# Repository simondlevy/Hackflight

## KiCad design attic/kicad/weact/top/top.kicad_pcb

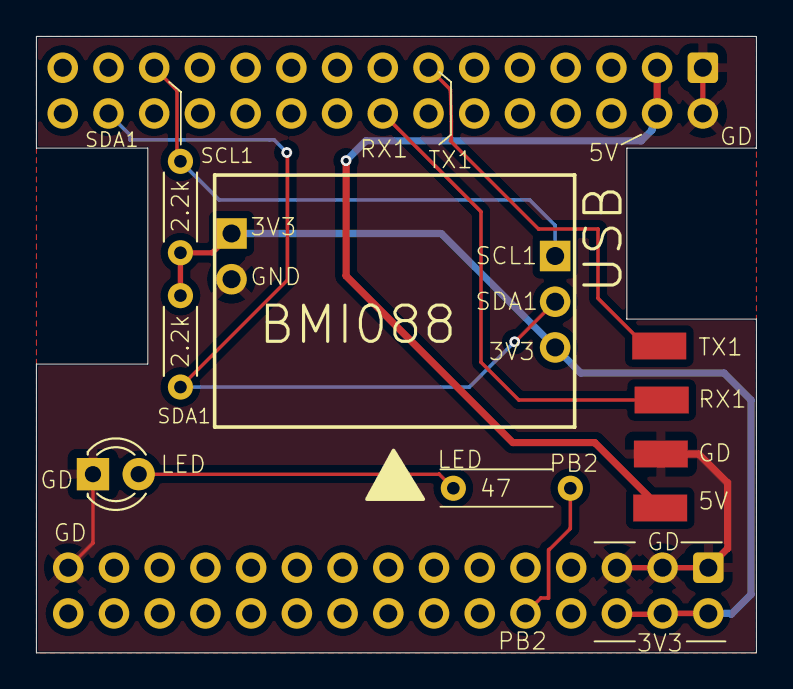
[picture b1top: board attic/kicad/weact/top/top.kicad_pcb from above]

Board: 2 copper layers, 40.0 x 34.2 mm, 12 parts (0 on the bottom side), 9 nets.

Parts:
2.2k, 2.2k#2: 2.2k Ohms; R_Axial_DIN0204_L3.6mm_D1.6mm_P5.08mm_Horizontal
47: 47 Ohms; R_Axial_DIN0204_L3.6mm_D1.6mm_P5.08mm_Horizontal
D1: LED; LED_D3.0mm
GND_PAD18, GND_PAD19, GND_PAD20, GND_PAD21: Conn_01x01; SolderWirePad_1x01_SMD_5x10mm
J1, J1#2: Conn_01x15_MountingPin; IDC-Header_2x15_P2.54mm_Vertical
Motor5: Conn_01x03_Female; PinHeader_1x03_P2.54mm_Vertical
PMW3901_PWR2: Conn_01x02_Female; PinHeader_1x02_P2.54mm_Vertical

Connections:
/3V3: 2.2k.2, 2.2k#2.2, J1.2, J1.4, J1.6, Motor5.3, PMW3901_PWR2.1
/5V: GND_PAD19.1, J1#2.3, J1#2.4
/GND: D1.1 (K), GND_PAD18.1, J1.1, J1.3, J1.5, J1.29, J1#2.1, J1#2.2, PMW3901_PWR2.2
/LED_RAW: 47.2, J1.10
/RX1: GND_PAD20.1, J1#2.16
/SCL1: 2.2k.1, J1#2.25, Motor5.1
/SDA1: 2.2k#2.1, J1#2.28, Motor5.2
/TX1: GND_PAD21.1, J1#2.13
unnamed: 47.1, D1.2 (A)

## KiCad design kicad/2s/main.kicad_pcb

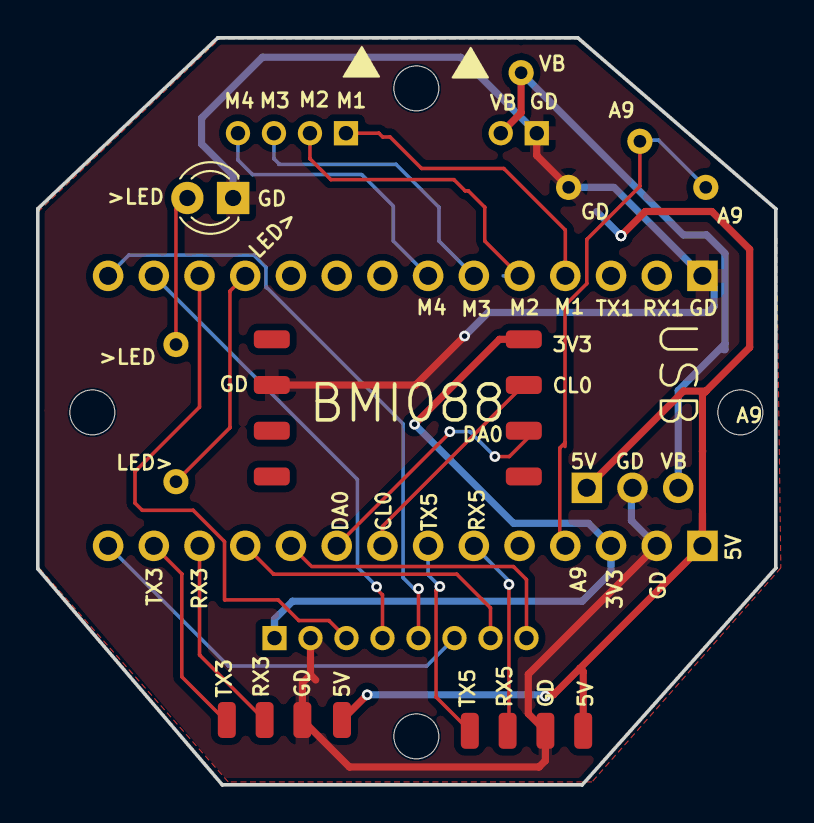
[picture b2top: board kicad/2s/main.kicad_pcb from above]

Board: 2 copper layers, 41.0 x 41.5 mm, 30 parts (0 on the bottom side), 23 nets.

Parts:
D1: LED; LED_D3.0mm_FlatTop
H1, H2, H3, H4: MountingHole; MountingHole_2.5mm
J1: Conn_01x14; PinSocket_1x14_P2.54mm_Vertical
J2: Conn_01x14_Socket; PinSocket_1x14_P2.54mm_Vertical
J3, J5, J7, J8, J9, J10, J11, J12, J13, J14, J17, J18, J19, J20, J21, J22: Conn_01x01_Pin; SolderWirePad_1x01_SMD_1x2mm
J4: Conn_01x03_Socket; PinHeader_1x03_P2.54mm_Vertical
J6: Conn_01x08; PinSocket_1x08_P2.00mm_Vertical
J15: Conn_01x02; PinSocket_1x02_P2.00mm_Vertical
J16: Conn_01x04; PinSocket_1x04_P2.00mm_Vertical
R1: R_LED; R_Axial_DIN0204_L3.6mm_D1.6mm_P7.62mm_Horizontal
R2: R1; R_Axial_DIN0204_L3.6mm_D1.6mm_P7.62mm_Horizontal
R3: R2; R_Axial_DIN0204_L3.6mm_D1.6mm_P7.62mm_Horizontal

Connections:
/3V3: J2.3, J6.1, J10.1 (Pin_1_1)
/5V: J2.1, J4.1, J14.1 (Pin_1_1), J20.1 (Pin_1_1)
/A9: J2.4, R2.1, R3.2
/CS: J1.12, J6.3
/GND: D1.1 (K), J1.1, J2.2, J3.1 (Pin_1_1), J4.2, J5.1 (Pin_1_1), J6.2, J15.1, J19.1 (Pin_1_1), R3.1
/LED: J1.11, R1.2
/M1: J1.4, J16.1
/M2: J1.5, J16.2
/M3: J1.6, J16.3
/M4: J1.7, J16.4
/MISO: J1.14, J6.5
/MOSI: J1.13, J6.4
/RX3: J2.12, J17.1 (Pin_1_1)
/RX5: J2.6, J21.1 (Pin_1_1)
/SCK: J2.14, J6.6
/SCL0: J2.8, J11.1 (Pin_1_1)
/SCL1: J2.11, J6.7
/SDA0: J2.9, J12.1 (Pin_1_1)
/SDA1: J2.10, J6.8
/TX3: J2.13, J18.1 (Pin_1_1)
/TX5: J2.7, J22.1 (Pin_1_1)
/VBAT: J4.3, J15.2, R2.2
unnamed: D1.2 (A), R1.1

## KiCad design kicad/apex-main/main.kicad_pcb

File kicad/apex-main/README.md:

# BOM, in order of soldering

Note: I recommend using Scotch tape to mask the pins you're not currently
soldering, and doing a continunity check for bridges/shorts after each step:

1. [Pololu 5V Step-Up/Step-Down Voltage Regulator S7V7F5](https://www.pololu.com/product/2119), on bottom, using 1-2mm chisel/bevel tip.

2. [28AWG silicone-insulated wire](https://www.amazon.com/BOJACK-Flexible-Silicone-Electric-Stripper/dp/B09Y89X5CV) for hover-deck, 
   protruding from bottom, using 0.2-0.8mm fine/conical tip.

3. [SHUTTLE BOARD 3.0 BMI088](https://www.digikey.com/en/products/detail/bosch-sensortec/SHUTTLE-BOARD-3-0-BMI088/14617528), on top, 
using 0.2-0.8mm fine/conical tip.  To avoid soldering a bridge (short circuit), you should solder only the four indicated
pins (3V3, GND, SDA, SCL), and in the bottom corners for added mounting security.

4. 28AWG silicone-insulates wires to 4-in-1 ESC, protruding from bottom, using 0.2-0.8mm fine/conical tip.
Most 4-in-1 ESCs come with this [connector](../../media/4-in-1-esc-wiring.jpg), or you can build one yourself
using a kit like
[this](https://www.amazon.com/Teansic-Connector-Pre-Crimped-Housing-Controller/dp/B0D5X6BY5Z/ref=sr_1_1_sspa?crid=1UNL8YQMAGJI0).

5. 220Ω resitor, on bottom, using 1-2mm chisel/bevel tip.

6. [LED](https://lighthouseleds.com/1-8mm-2mm-led-red-ultra-bright.html), on top, using 1-2mm chisel/bevel tip.

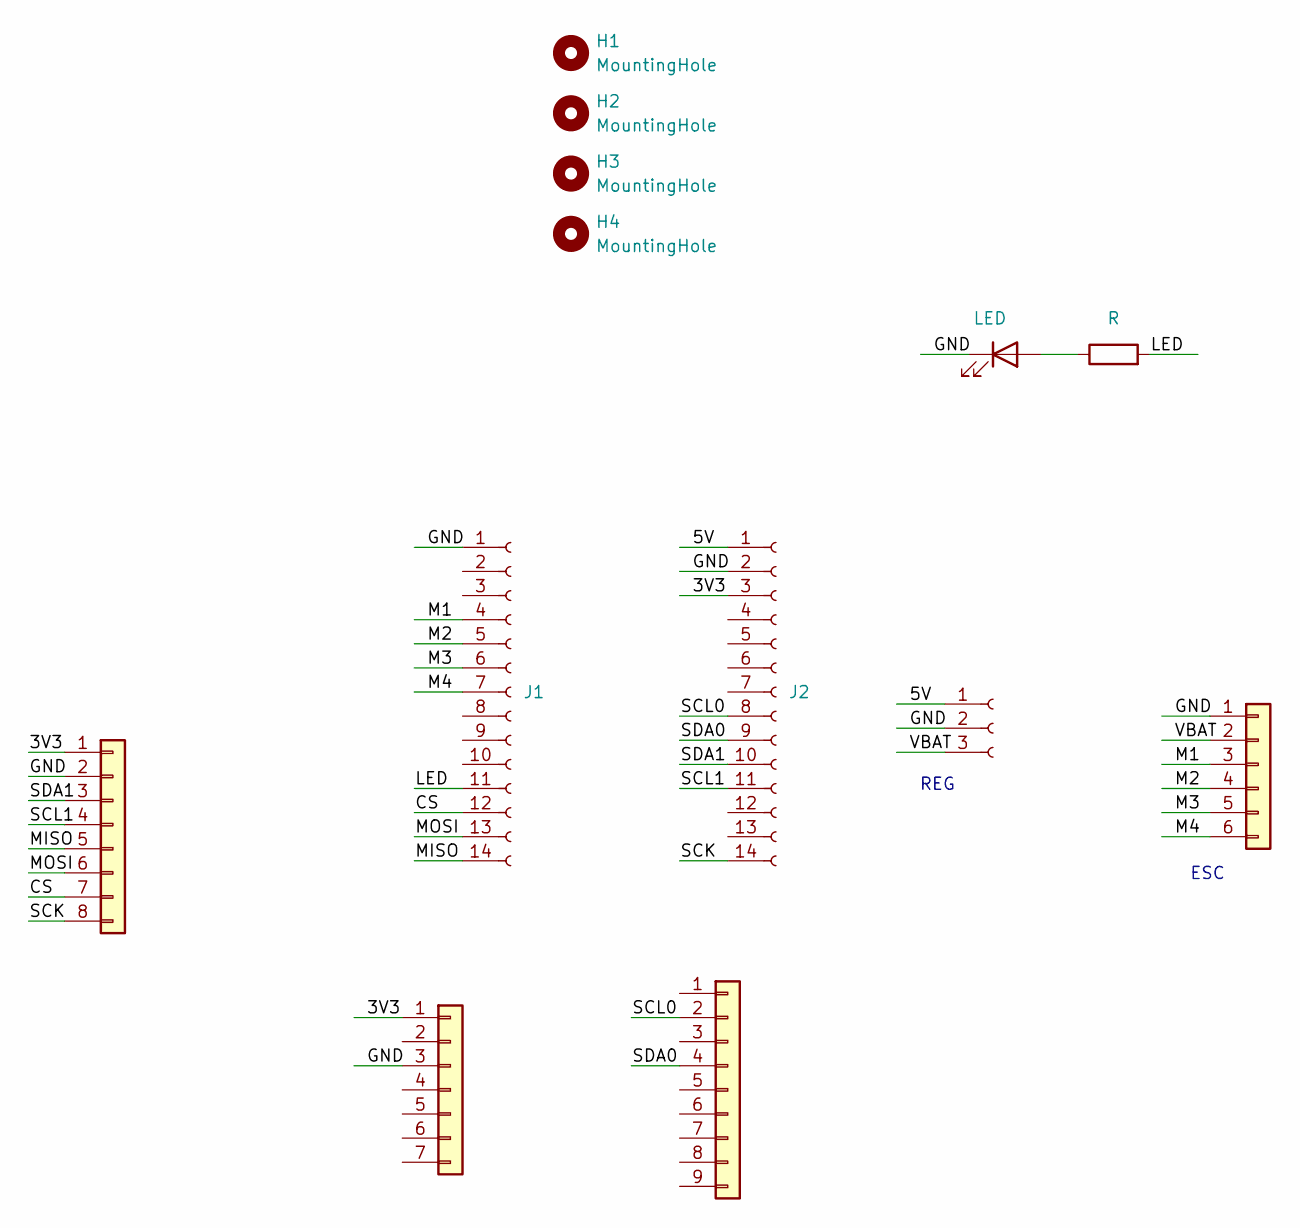
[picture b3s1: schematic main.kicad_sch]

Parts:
D1: LED; LED_D3.0mm_FlatTop
H1, H2, H3, H4: MountingHole; MountingHole_2.1mm
J1: Conn_01x14; PinSocket_1x14_P2.54mm_Vertical
J2: Conn_01x14_Socket; PinSocket_1x14_P2.54mm_Vertical
J4: Conn_01x03_Socket; PinHeader_1x03_P2.54mm_Vertical
J5: Conn_01x06; PinSocket_1x06_P2.00mm_Vertical
J6: Conn_01x08; PinSocket_1x08_P2.00mm_Vertical
J7: Conn_01x07; PinHeader_1x07_P1.27mm_Vertical
J8: Conn_01x09; PinHeader_1x09_P1.27mm_Vertical
R1: R; R_Axial_DIN0204_L3.6mm_D1.6mm_P7.62mm_Horizontal

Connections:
/3V3: J2.3, J6.1, J7.1
/5V: J2.1, J4.1
/CS: J1.12, J6.7
/GND: D1.1 (K), J1.1, J2.2, J4.2, J5.1, J6.2, J7.3
/LED: J1.11, R1.2
/M1: J1.4, J5.3
/M2: J1.5, J5.4
/M3: J1.6, J5.5
/M4: J1.7, J5.6
/MISO: J1.14, J6.5
/MOSI: J1.13, J6.6
/SCK: J2.14, J6.8
/SCL0: J2.8, J8.2
/SCL1: J2.11, J6.4
/SDA0: J2.9, J8.4
/SDA1: J2.10, J6.3
/VBAT: J4.3, J5.2
unnamed: D1.2 (A), R1.1

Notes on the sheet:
ESC
REG

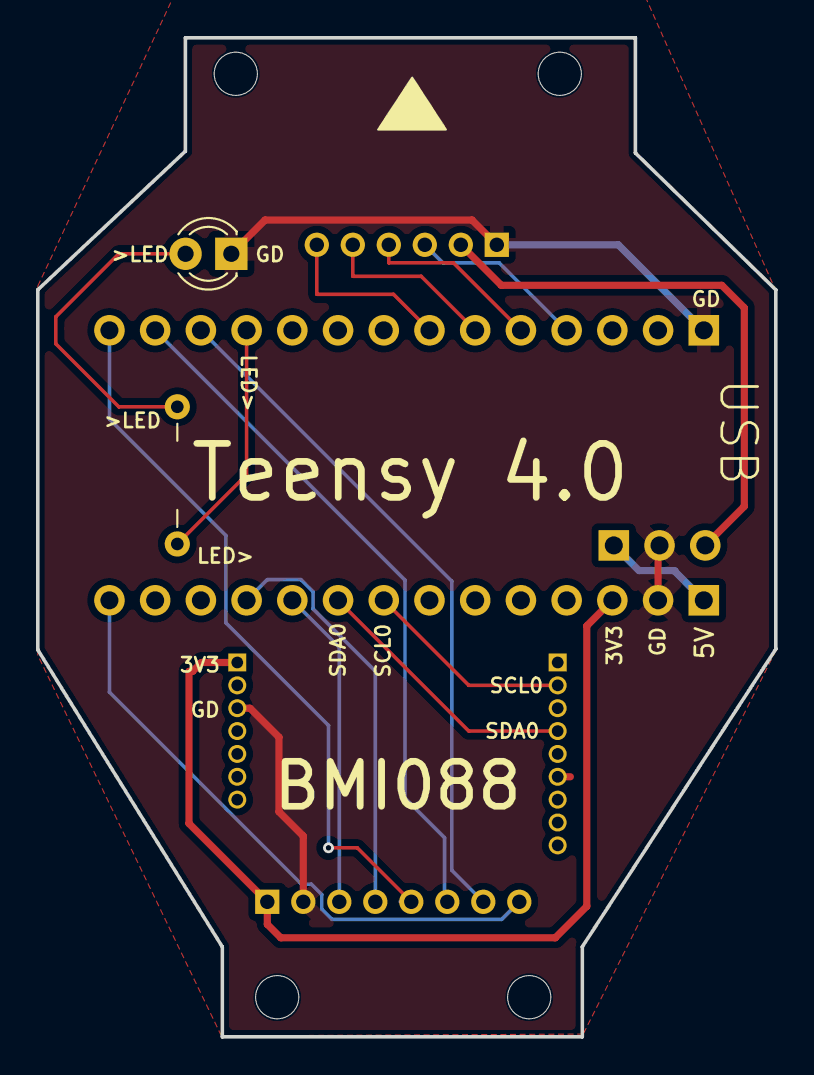
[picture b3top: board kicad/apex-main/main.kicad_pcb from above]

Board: 2 copper layers, 41.0 x 55.5 mm, 16 parts (0 on the bottom side), 18 nets.

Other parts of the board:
H1#2, H1#3, H1#4: MountingHole; MountingHole_2.1mm

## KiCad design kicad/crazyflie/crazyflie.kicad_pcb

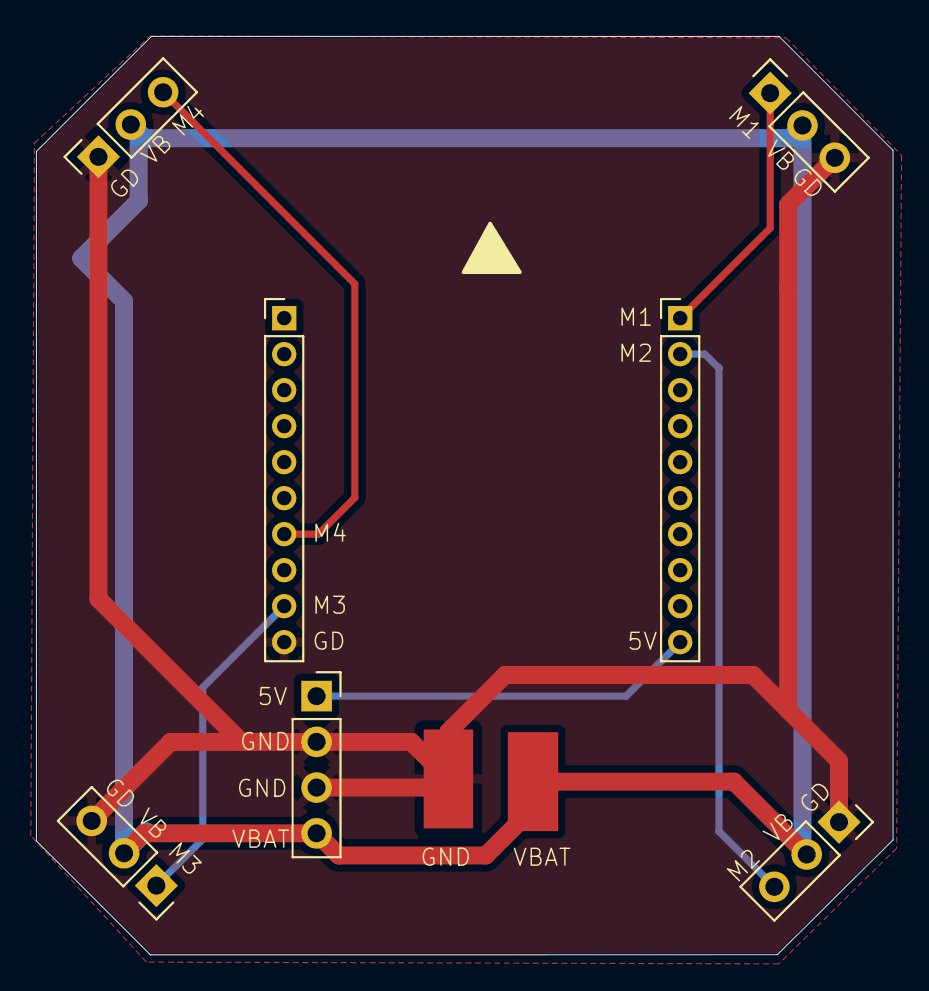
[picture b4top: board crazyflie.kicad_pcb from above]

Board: 2 copper layers, 47.6 x 51.0 mm, 9 parts (0 on the bottom side), 7 nets.

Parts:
GND_PAD1: Conn_01x01; SolderWirePad_1x01_SMD_5x10mm
J1, J2: Conn_01x10_Female; PinHeader_1x10_P2.00mm_Vertical
J8: Conn_01x04_Socket; PinSocket_1x04_P2.54mm_Vertical
M1, M2, M3, M4: Conn_01x03_Socket; PinSocket_1x03_P2.54mm_Vertical
VB_PAD1: Conn_01x01; SolderWirePad_1x01_SMD_5x10mm

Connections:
/5V: J2.10, J8.1
/GND: GND_PAD1.1, J1.10, J8.2, J8.3, M1.3, M2.1, M3.3, M4.1
/M1: J2.1, M1.1
/M2: J2.2, M2.3
/M3: J1.9, M3.1
/M4: J1.7, M4.3
/VBAT: J8.4, M1.2, M2.2, M3.2, M4.2, VB_PAD1.1

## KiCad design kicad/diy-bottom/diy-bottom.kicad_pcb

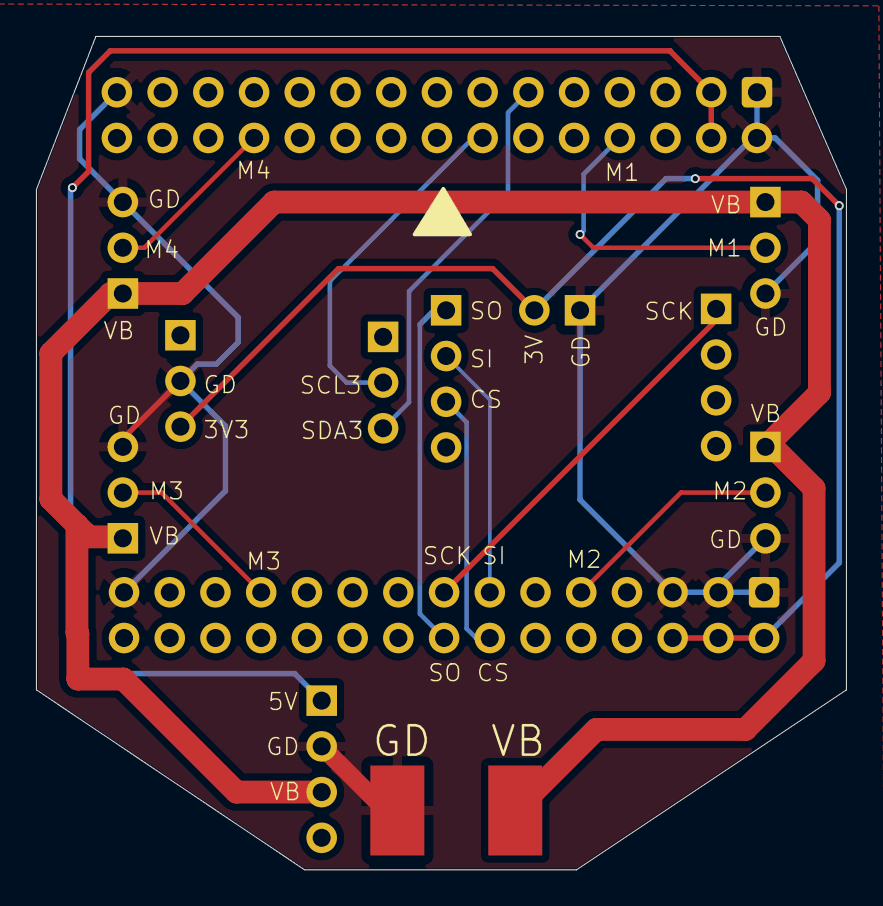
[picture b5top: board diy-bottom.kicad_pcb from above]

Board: 2 copper layers, 45.0 x 46.3 mm, 14 parts (0 on the bottom side), 14 nets.

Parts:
GND_PAD1: Conn_01x01; SolderWirePad_1x01_SMD_5x10mm
J1, J2: Conn_01x15_MountingPin; IDC-Header_2x15_P2.54mm_Vertical
PMW3901_L1, PMW3901_R1: Conn_01x04_Female; PinSocket_1x04_P2.54mm_Vertical
PMW3901_PWR1: Conn_01x02_Female; PinHeader_1x02_P2.54mm_Vertical
REG1: Conn_01x04_Female; PinSocket_1x04_P2.54mm_Vertical
VB_PAD1: Conn_01x01; SolderWirePad_1x01_SMD_5x10mm
VL53L1_L2, VL53L1_L3, VL53L1_L4, VL53L1_L5, VL53L1_R1, VL53L1_R2: Conn_01x03_Female; PinHeader_1x03_P2.54mm_Vertical

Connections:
/3V3: J2.2, J2.4, J2.6, PMW3901_PWR1.2, VL53L1_R2.3
/5V: J1.3, J1.4, REG1.1
/CS: J2.14, PMW3901_R1.3
/GND: GND_PAD1.1, J1.1, J1.2, J1.29, J2.1, J2.3, J2.5, J2.29, PMW3901_PWR1.1, REG1.2, VL53L1_L2.3, VL53L1_L3.3, VL53L1_L4.3, VL53L1_L5.3, VL53L1_R2.2
/M1: J1.8, VL53L1_L2.2
/M2: J2.9, VL53L1_L3.2
/M3: J2.23, VL53L1_L5.2
/M4: J1.24, VL53L1_L4.2
/MISO: J2.16, PMW3901_R1.1
/MOSI: J2.13, PMW3901_R1.2
/SCK: J2.15, PMW3901_L1.1
/SCL3: J1.14, VL53L1_R1.2
/SDA3: J1.11, VL53L1_R1.3
/VBAT: REG1.3, VB_PAD1.1, VL53L1_L2.1, VL53L1_L3.1, VL53L1_L4.1, VL53L1_L5.1

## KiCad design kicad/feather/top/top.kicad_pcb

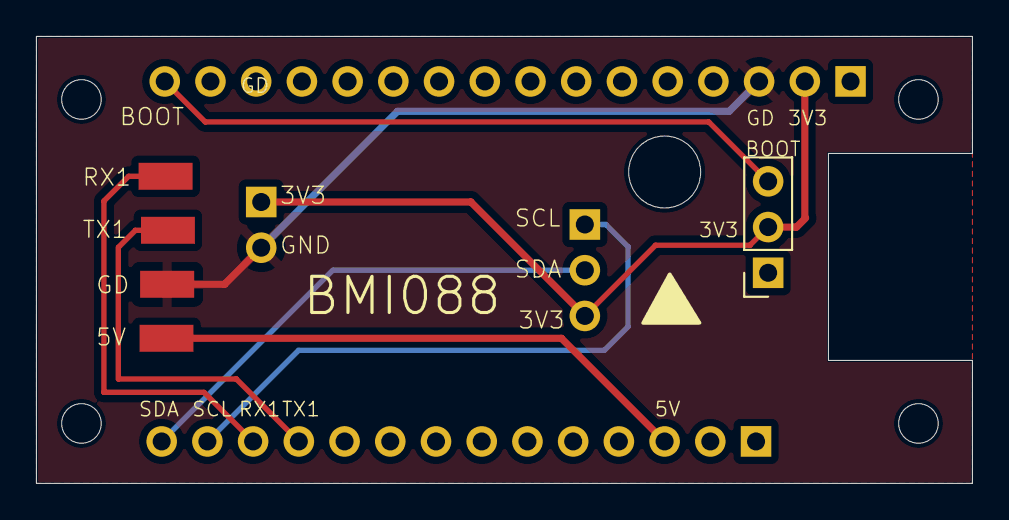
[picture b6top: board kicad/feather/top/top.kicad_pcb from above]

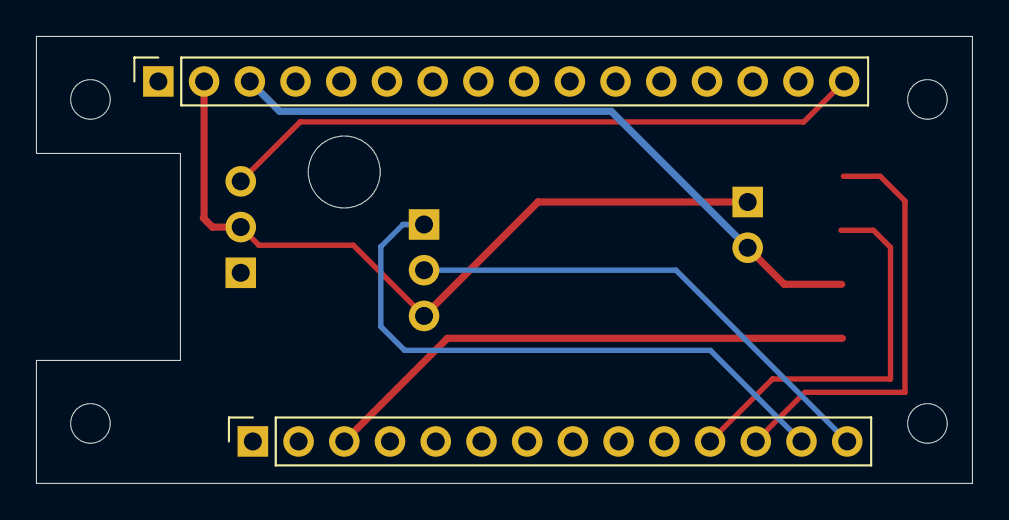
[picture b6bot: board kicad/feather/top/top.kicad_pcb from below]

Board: 2 copper layers, 52.0 x 24.8 mm, 14 parts (2 on the bottom side), 8 nets.

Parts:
GND_PAD18, GND_PAD19, GND_PAD20, GND_PAD21: Conn_01x01; SolderWirePad_1x01_SMD_5x10mm
J1: Conn_01x12_Socket; PinSocket_1x14_P2.54mm_Vertical
J2: Conn_01x16_Socket; PinSocket_1x16_P2.54mm_Vertical
J3: Conn_01x03_Socket; PinSocket_1x03_P2.54mm_Vertical
Motor5: Conn_01x03_Female; PinHeader_1x03_P2.54mm_Vertical
PMW3901_PWR2: Conn_01x02_Female; PinHeader_1x02_P2.54mm_Vertical
POST_1, POST_2, POST_3, POST_4: MountingHole; MountingHole_2.2mm_M2
POST_5: MountingHole; MountingHole_4mm

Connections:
/3V3: J2.2, J3.2, Motor5.3, PMW3901_PWR2.1
/5V: GND_PAD19.1, J1.3
/BOOT: J2.16, J3.3
/GND: GND_PAD18.1, J2.3, PMW3901_PWR2.2
/RX1: GND_PAD21.1, J1.12
/SCL: J1.13, Motor5.1
/SDA: J1.14, Motor5.2
/TX1: GND_PAD20.1, J1.11

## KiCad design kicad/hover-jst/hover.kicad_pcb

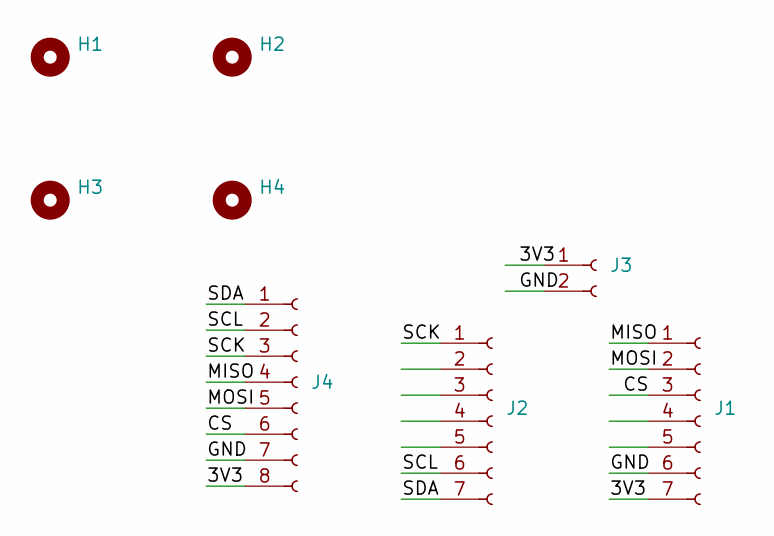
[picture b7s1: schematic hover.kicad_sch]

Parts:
H1, H2, H3, H4: MountingHole; MountingHole_2.5mm
J1, J2: Conn_01x07_Socket; PinSocket_1x07_P2.54mm_Vertical
J3: Conn_01x02_Socket; PinSocket_1x02_P2.54mm_Vertical
J4: Conn_01x08_Socket; JST_SHL_SM08B-SHLS-TF_1x08-1MP_P1.00mm_Horizontal

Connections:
/3V3: J1.7, J3.1, J4.8
/CS: J1.3, J4.6
/GND: J1.6, J3.2, J4.7
/MISO: J1.1, J4.4
/MOSI: J1.2, J4.5
/SCK: J2.1, J4.3
/SCL: J2.6, J4.2
/SDA: J2.7, J4.1

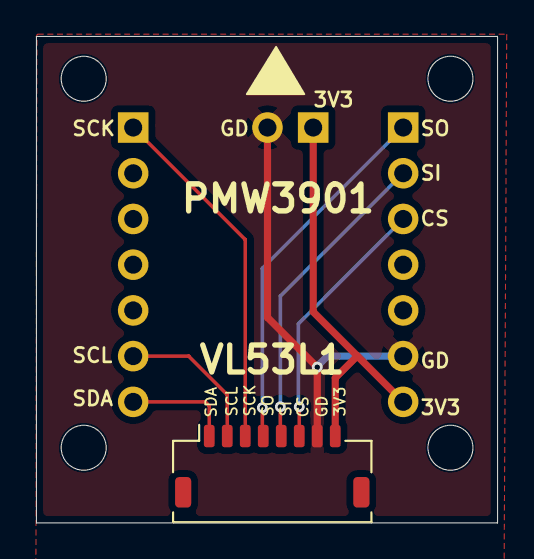
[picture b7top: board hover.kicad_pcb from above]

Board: 2 copper layers, 25.6 x 27.0 mm, 8 parts (0 on the bottom side), 8 nets.
